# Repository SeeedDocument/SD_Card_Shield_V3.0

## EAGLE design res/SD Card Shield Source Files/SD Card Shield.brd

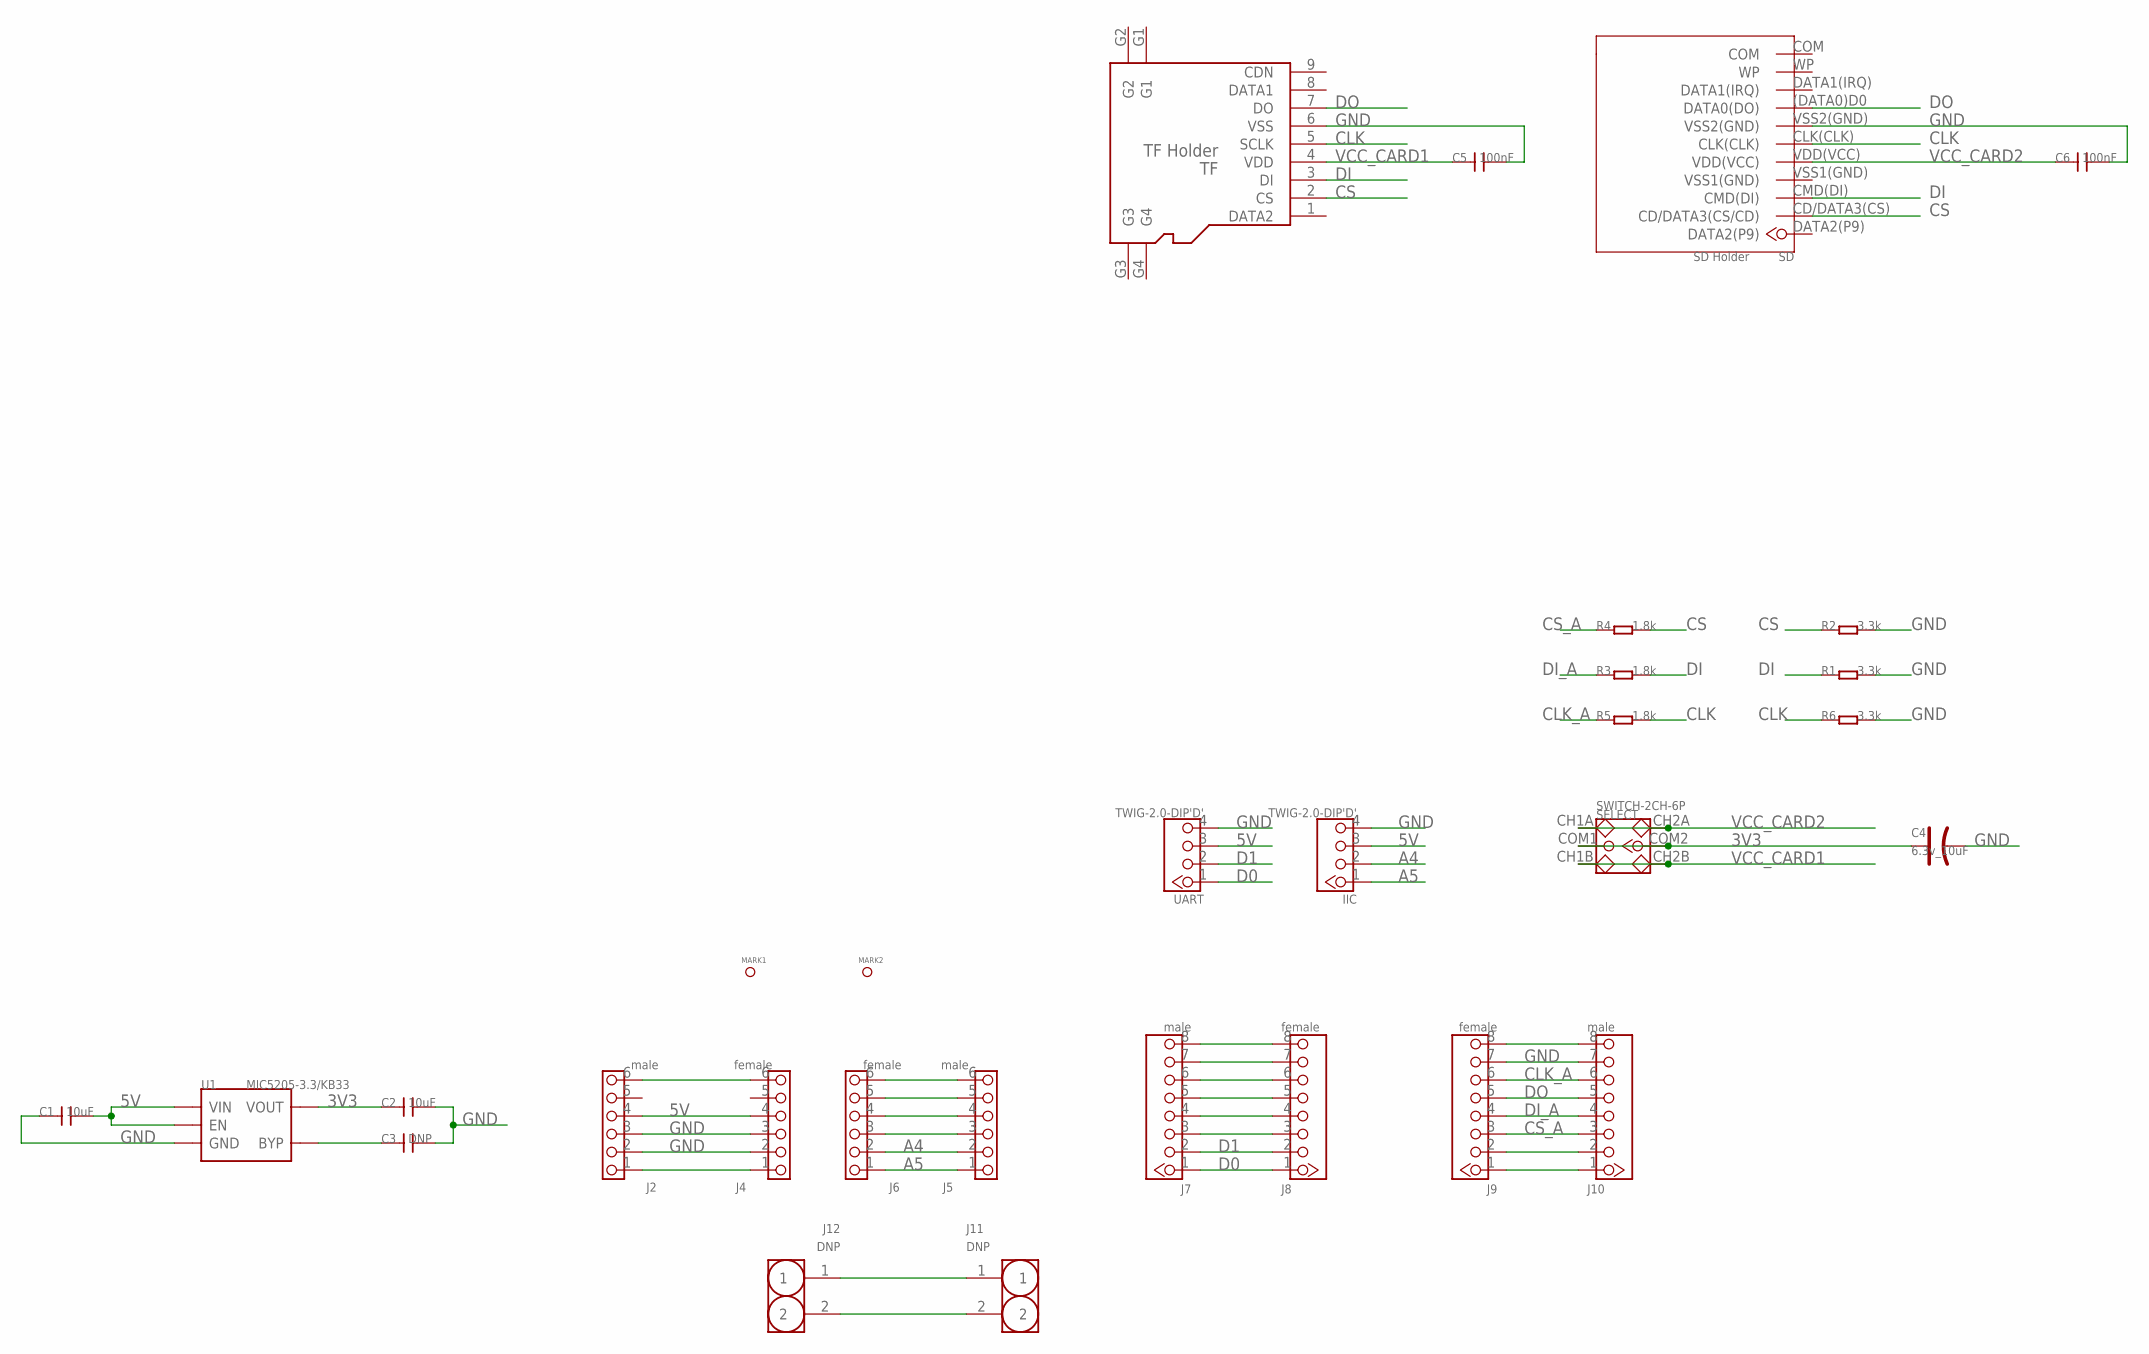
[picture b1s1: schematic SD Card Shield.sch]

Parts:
C1, C2: 10uF; 0805
C3: DNP; 0603
C4: 6.3v_10uF; AVX-A
C5, C6: 100nF; 0603
IIC: TWIG-2.0-DIP'D'; 2.0_1X4_90
J2, J5: male; 2.54_6P
J4, J6: female; 2.54_6P
J7, J10: male; CK_1X8
J8, J9: female; CK_1X8
J11, J12: DNP; 65*35
MARK1, MARK2: DNP; ROUND-MARK-1.0
R1, R2, R6: 3.3k; 0603
R3, R4, R5: 1.8k; 0603
SD: SD Holder; SDCARDEXTPACKAGE
SELECT: SWITCH-2CH-6P; 6P-2CH-2.54-7.6X3.0
TF: TF Holder; 9P-SMD-W/-RING
U1: MIC5205-3.3/KB33; SOT23-5
UART: TWIG-2.0-DIP'D'; 2.0_1X4_90

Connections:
3V3: C2.1, C4.+, SELECT.COM1, SELECT.COM2, U1.5 (VOUT)
5V: C1.2, IIC.3, J2.4, J4.4, U1.1 (VIN), U1.3 (EN), UART.3
A4: IIC.2, J5.2, J6.2
A5: IIC.1, J5.1, J6.1
CLK: R5.2, R6.1, SD.CLK(CLK), TF.5 (SCLK)
CLK_A: J9.6, J10.6, R5.1
CS: R2.1, R4.2, SD.CD/DATA3(CS) (CD/DATA3(CS/CD)), TF.2 (CS)
CS_A: J9.3, J10.3, R4.1
D0: J7.1, J8.1, UART.1
D1: J7.2, J8.2, UART.2
DI: R1.1, R3.2, SD.CMD(DI), TF.3 (DI)
DI_A: J9.4, J10.4, R3.1
DO: J9.5, J10.5, SD.(DATA0)D0 (DATA0(DO)), TF.7 (DO)
GND: C1.1, C2.2, C3.2, C4.-, C5.2, C6.2, IIC.4, J2.2, J2.3, J4.2, J4.3, J9.7, J10.7, R1.2, R2.2, R6.2, SD.VSS2(GND), TF.6 (VSS), U1.2 (GND), UART.4
unnamed: J2.1, J4.1
unnamed: J11.1, J12.1
unnamed: J11.2, J12.2
unnamed: C3.1, U1.4 (BYP)
unnamed: J2.6, J4.6
unnamed: J5.3, J6.3
unnamed: J5.4, J6.4
unnamed: J5.5, J6.5
unnamed: J5.6, J6.6
unnamed: J7.3, J8.3
unnamed: J7.4, J8.4
unnamed: J7.5, J8.5
unnamed: J7.6, J8.6
unnamed: J7.7, J8.7
unnamed: J7.8, J8.8
unnamed: J9.2, J10.2
unnamed: J9.8, J10.8
unnamed: J9.1, J10.1
VCC_CARD1: C5.1, SELECT.CH1B, SELECT.CH2B, TF.4 (VDD)
VCC_CARD2: C6.1, SD.VDD(VCC), SELECT.CH1A, SELECT.CH2A

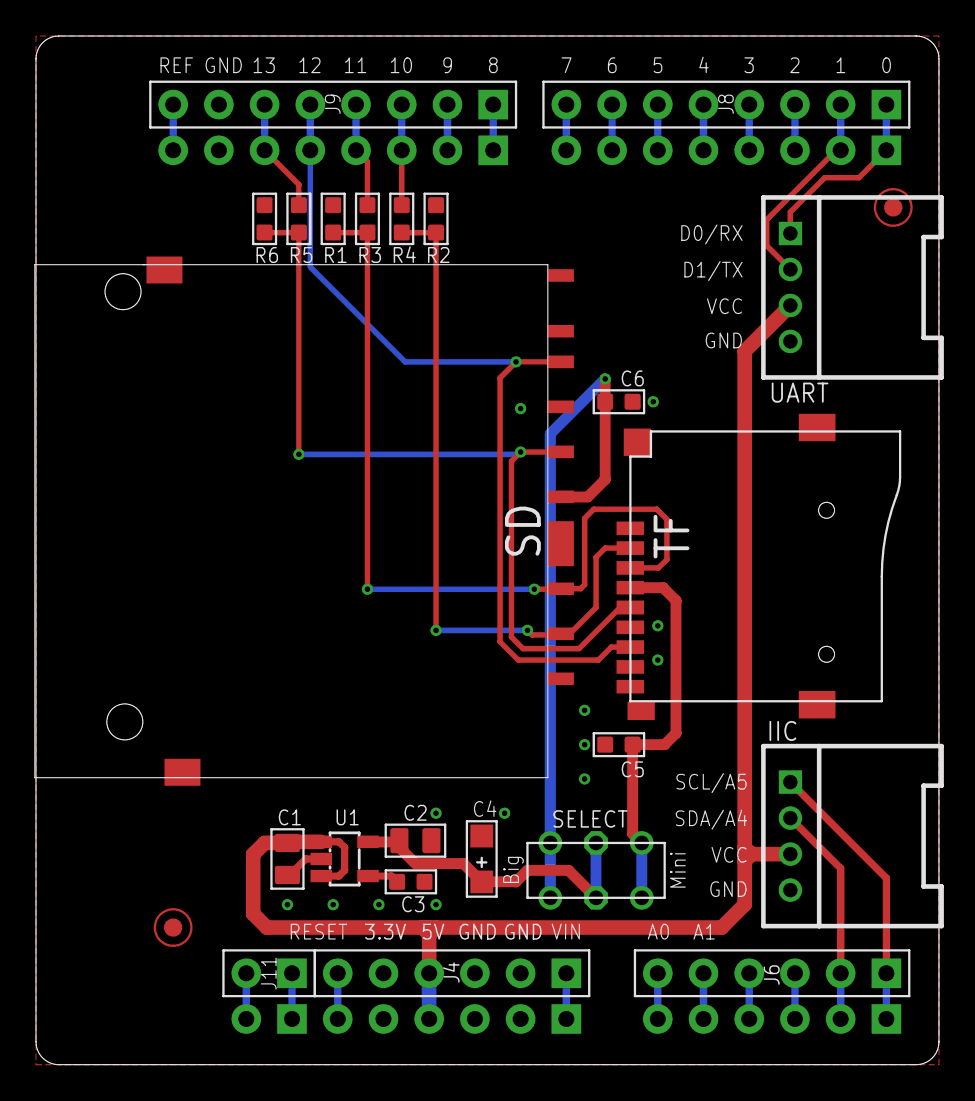
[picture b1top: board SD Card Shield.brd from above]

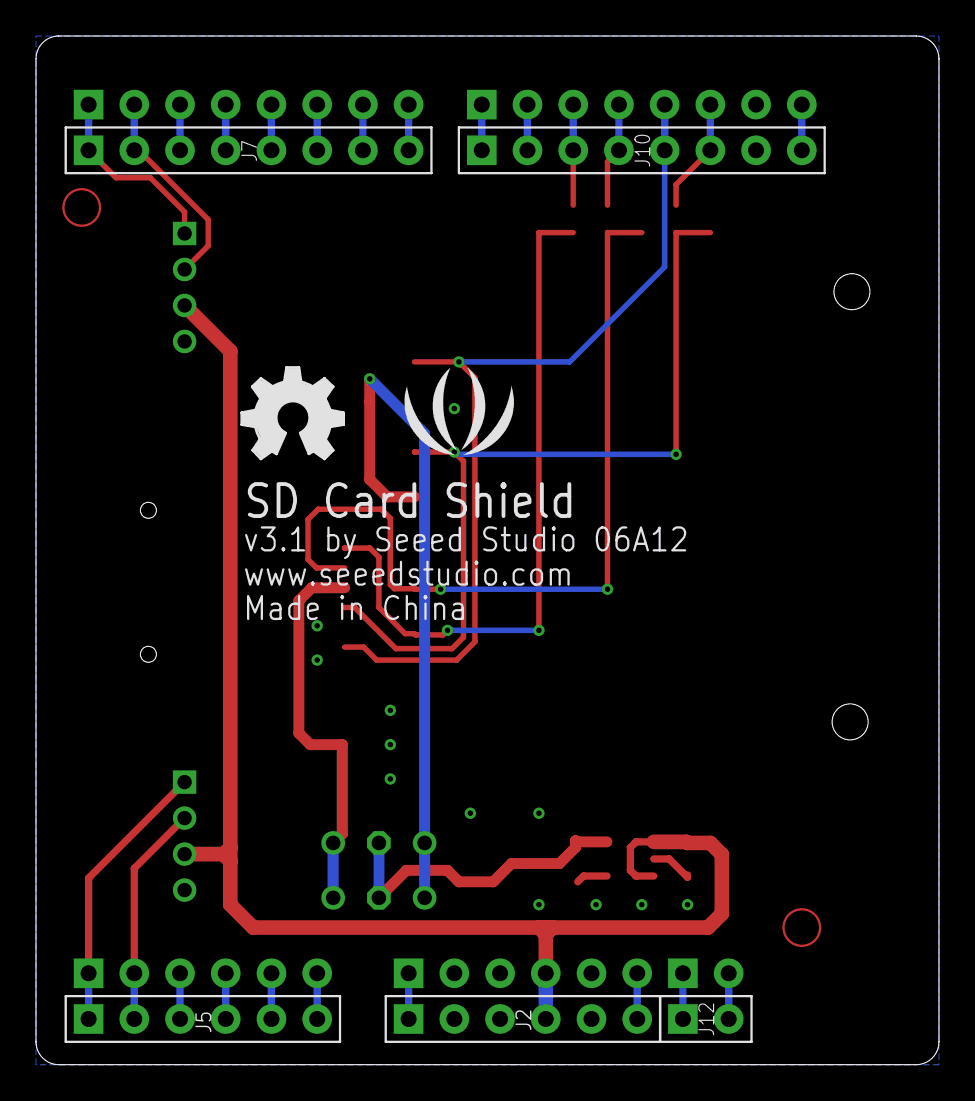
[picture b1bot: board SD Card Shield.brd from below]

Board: 2 copper layers, 50.2 x 57.1 mm, 32 parts (7 on the bottom side), 34 nets.

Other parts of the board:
U$1: LOGO_SILK
U$2: OSHW_FILLX200_NOTEXT

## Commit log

2017-06-13 upgrade
